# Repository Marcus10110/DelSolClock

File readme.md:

# Del Sol Clock

This is a project to replace the clock in my car with an ESP32 and a small display.

The replacement clock screen will display time, the currently playing music, and iOS notifications.

Bluetooth low energy is used to communicate with a phone.
Note, some services should support any BLE phone, for example the current time service. However the Apple Media Service and the notification service only support iOS.

## Features

### Apple Media Service

This displays the current playback information from the iPhone. It doesn't currently support playback controls (e.g. next/previous track).

[Apple Documentation.](https://developer.apple.com/library/archive/documentation/CoreBluetooth/Reference/AppleMediaService_Reference/Specification/Specification.html#//apple_ref/doc/uid/TP40014716-CH1-SW7)

Special thanks to the following examples. As far as I can tell, this hasn't been implemented using the [Arduino ESP32 board library](https://github.com/espressif/arduino-esp32) before.

- [James Hudson's Apple Notification Center Service](https://github.com/Smartphone-Companions/ESP32-ANCS-Notifications/blob/master/src/ancs_ble_client.cpp) This example finally showed how to solicit services using the Arduino ESP32 library, which is not built-in.
- [John Park's Adafruit Guide to the Apple Media Service Display](https://learn.adafruit.com/now-playing-bluetooth-apple-media-service-display/apple-music-service) This was the first working example I could find. Written in CircutPython.
- [Moddable's Apple Media Service example](https://github.com/Moddable-OpenSource/moddable/blob/6d7f33f8f318663bd5ba8d6ca6536443d42e68ea/modules/network/ble/ams-client/amsclient.js#L129) This was another good example, written in javascript.

### Current Time Service

This gets the current time.

[Current Time Service Documentation](https://www.bluetooth.com/specifications/specs/current-time-service-1-1/)

Note, the documentation is split over several PDFs. See CurrentTimeService.cpp for more documentation links.

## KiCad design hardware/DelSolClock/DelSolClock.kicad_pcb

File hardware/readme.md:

# Hardware

The Del Sol Clock PCBs are designed to be direct replacements for the stock clock PCBs found in the original dash clock.

There are two PCBs in the clock housing. The front PCB, which contains pretty everything, and a rear PCB, which is largely responsible for the electrical connections to the car.

The two PCBs are designed with KiCad. The front PCB is located in the `./DelSolClock` directory, and the rear PCB is located in `./DelSolClock-Rear` directory.

## Front PCB

Schematic:

Divider Circuit:

This divider circuit is used to shift the 12V signal down to 3.3V without engaging over voltage protection. It uses a ~3.6 volt Zener diode to clamp the voltage, which is preferred over regular rail clamps to prevent damage if the supply voltage is not present when a 12V input is applied.

PCB:

## Rear PCB

The rear PCB contains a 12V to 3.3V buck converter module, to provide power to the front PCB, and routes all the car IO signals to the front PCB.

The front PCB is connected to the read PCB with a short 8 pin ribbon cable.

The rear PCB also contains diodes for the Trunk, Roof, and Window signals, to prevent backfeeding into the car's electrical system.

The following signals are provided by the car:

- 12V Power (battery, always hot)
- Ground
- Ignition (IGN)
- Rear Window
- Roof removed
- Trunk Open
- Dash Illumination (ILL)

Rear window, roof removed, and trunk open are open drain signals, which either float or get connected to ground when active. The stock dash clock contained indicator LEDs connected to these signals.

Ignition is also an active high signal, which is only high when the ignition is on. I think it floats when not active.

Dash illumination is connected to the dash's lights, which are dimmable, but only on when the headlights are on. This controlled the brightness of the original dash clock's display. When the headlights are off, the stock clock would run at max brightness.

Schematic:

PCB:

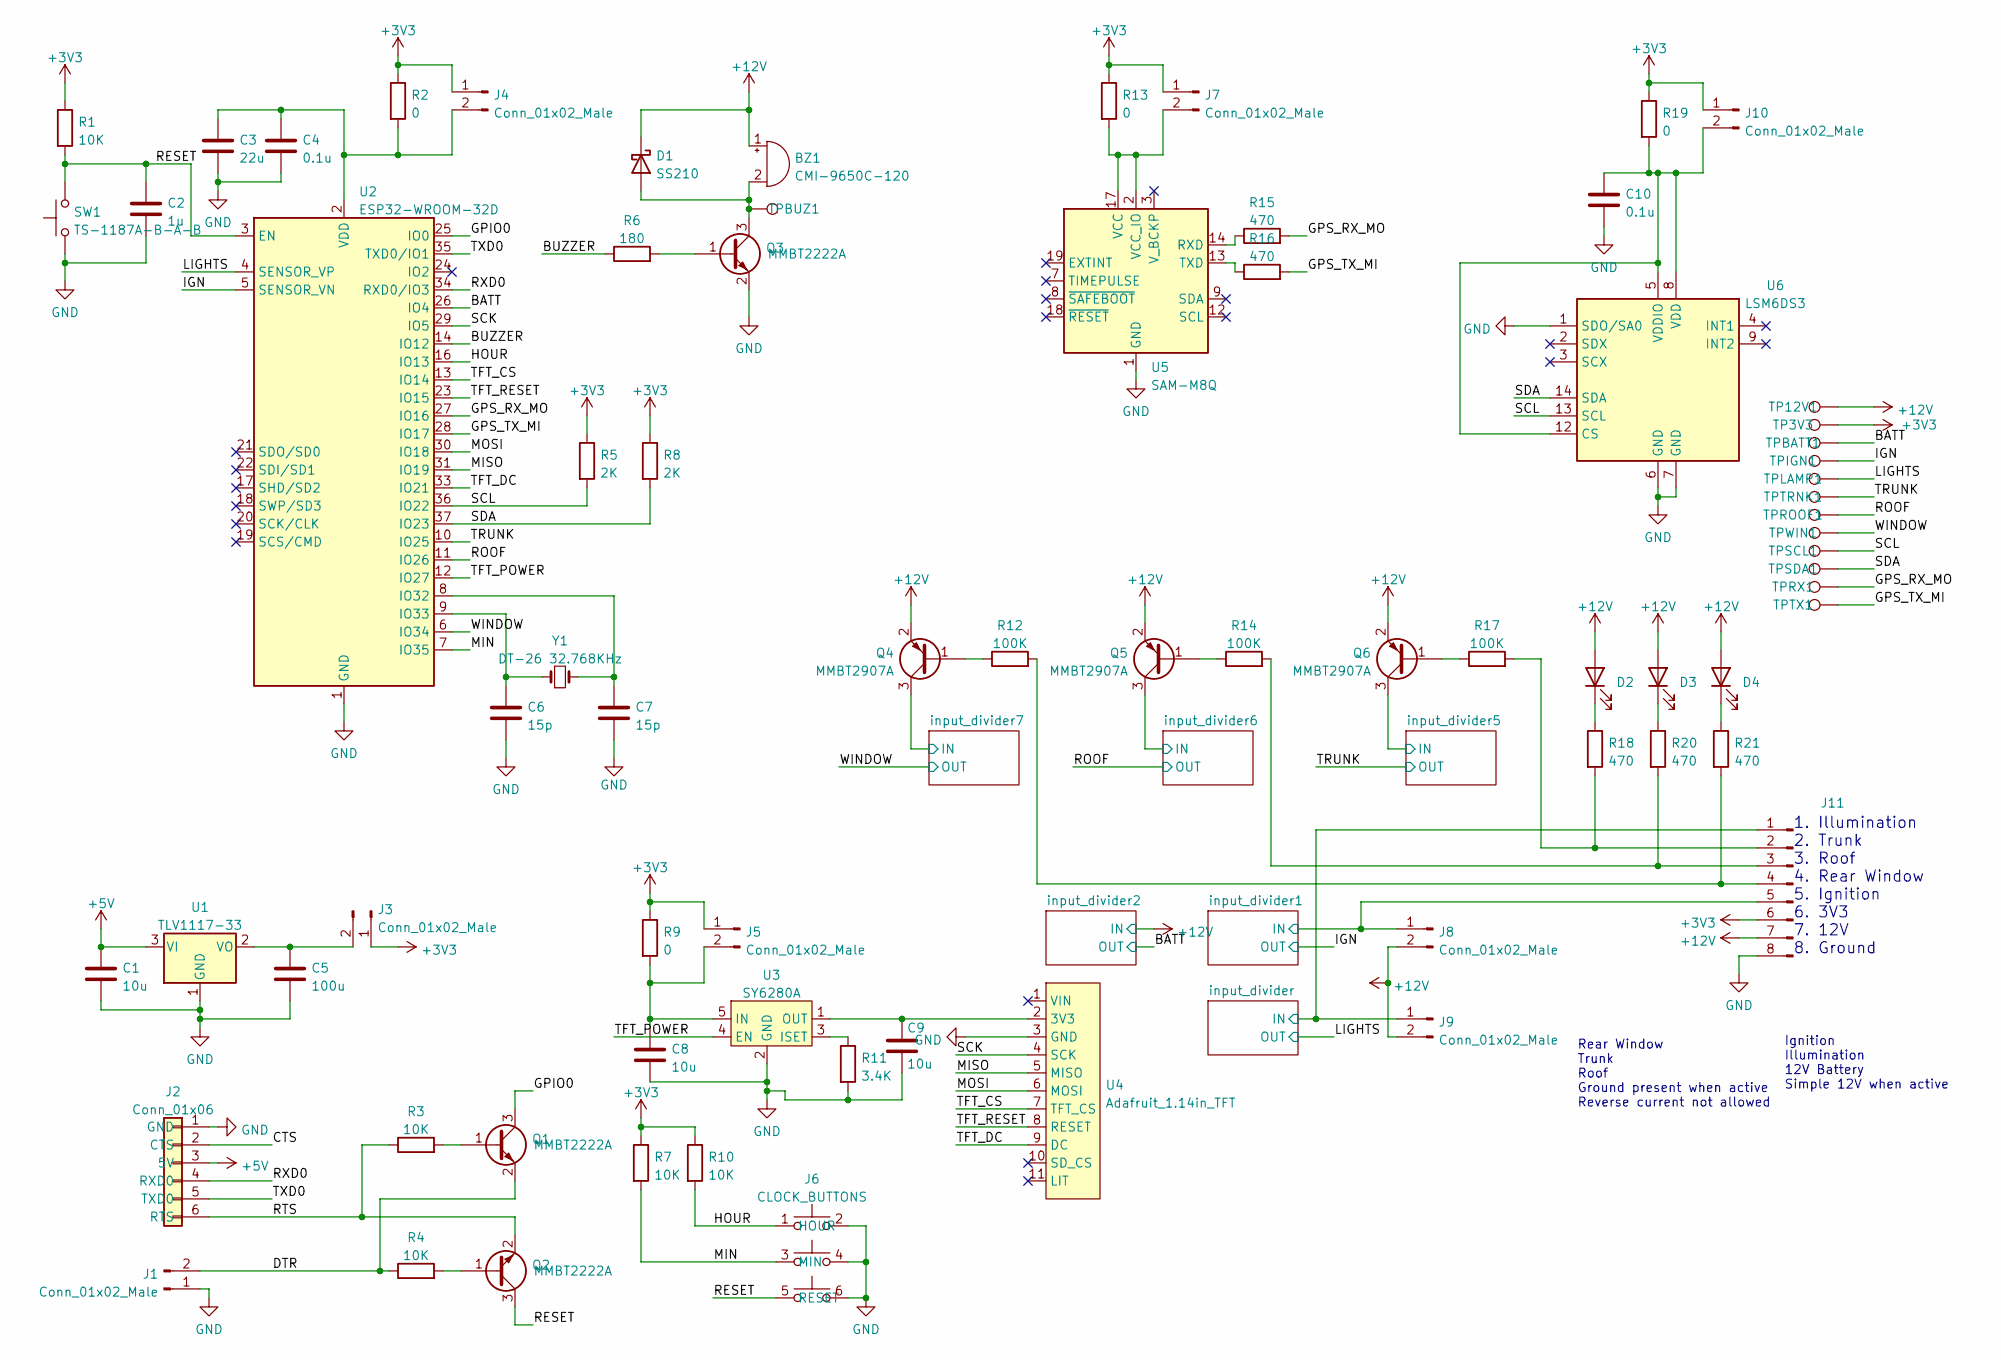
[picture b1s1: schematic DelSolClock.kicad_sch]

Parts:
BZ1: CMI-9650C-120; Buzzer_CUI-CMI-9650C-120
C1, C8, C9: 10u; C_0805_2012Metric_Pad1.18x1.45mm_HandSolder
C2: 1u; C_0805_2012Metric_Pad1.18x1.45mm_HandSolder
C3: 22u; C_0805_2012Metric_Pad1.18x1.45mm_HandSolder
C4, C10: 0.1u; C_0805_2012Metric_Pad1.18x1.45mm_HandSolder
C5: 100u; C_1206_3216Metric_Pad1.33x1.80mm_HandSolder
C6, C7: 15p; C_0805_2012Metric_Pad1.18x1.45mm_HandSolder
D1: SS210; D_SMA_Handsoldering
D2, D3: SSL-LX4673ID-LA20; LED_Rectangular_W3.65mm_L6.15mm
D4: WP132XGD; LED_D3.0mm
J1, J3, J4, J5, J7, J8, J9, J10: Conn_01x02_Male; PinHeader_1x02_P2.54mm_Vertical
J2: Conn_01x06; PinHeader_1x06_P2.54mm_Vertical
J6: CLOCK_BUTTONS; Switch_DelSol
J11: Conn_01x08_Male; PinHeader_1x08_P2.54mm_Vertical
Q1, Q2, Q3: MMBT2222A; SOT-23
Q4, Q5, Q6: MMBT2907A; SOT-23
R1, R3, R4, R7, R10: 10K; R_0805_2012Metric_Pad1.20x1.40mm_HandSolder
R2, R9, R13, R19: 0; R_0805_2012Metric_Pad1.20x1.40mm_HandSolder
R5, R8: 2K; R_0805_2012Metric_Pad1.20x1.40mm_HandSolder
R6: 180; R_0805_2012Metric_Pad1.20x1.40mm_HandSolder
R11: 3.4K; R_0805_2012Metric_Pad1.20x1.40mm_HandSolder
R12, R14, R17: 100K; R_0805_2012Metric_Pad1.20x1.40mm_HandSolder
R15, R16, R18, R20, R21: 470; R_0805_2012Metric_Pad1.20x1.40mm_HandSolder
SW1: TS-1187A-B-A-B; SW_SPST_SKQG_WithoutStem
TP3V3, TP12V1: TestPoint; TestPoint_Keystone_5000-5004_Miniature
TPBATT1: TestPoint; TestPoint_Keystone_5000-5004_Miniature
TPBUZ1: TestPoint; TestPoint_Keystone_5000-5004_Miniature
TPIGN1: TestPoint; TestPoint_Keystone_5000-5004_Miniature
TPLAMP1: TestPoint; TestPoint_Keystone_5000-5004_Miniature
TPROOF1: TestPoint; TestPoint_Keystone_5000-5004_Miniature
TPRX1: TestPoint; TestPoint_Keystone_5000-5004_Miniature
TPSCL1: TestPoint; TestPoint_Keystone_5000-5004_Miniature
TPSDA1: TestPoint; TestPoint_Keystone_5000-5004_Miniature
TPTRNK1: TestPoint; TestPoint_Keystone_5000-5004_Miniature
TPTX1: TestPoint; TestPoint_Keystone_5000-5004_Miniature
TPWIN1: TestPoint; TestPoint_Keystone_5000-5004_Miniature
U1: TLV1117-33; SOT-223
U2: ESP32-WROOM-32D; ESP32-WROOM-32
U3: SY6280A; SOT-23-5
U4: Adafruit_1.14in_TFT
U5: SAM-M8Q; ublox_SAM-M8Q
U6: LSM6DS3; LGA-14_3x2.5mm_P0.5mm_LayoutBorder3x4y
Y1: DT-26 32.768KHz; Crystal_DS26_D2.0mm_L6.0mm_Horizontal_1EP_style1

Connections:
+3V3: J3.1, J4.1, J5.1, J7.1, J10.1, J11.6 (3V3), R1.1, R2.1, R5.1, R7.1, R8.1, R9.1, R10.1, R13.1, R19.1, TP3V3.1
+5V: C1.1, J2.3 (5V), U1.3 (VI)
+12V: BZ1.1 (-), D1.1 (K), D2.2 (A), D3.2 (A), D4.2 (A), J8.2, J9.2, J11.7 (12V), Q4.2 (E), Q5.2 (E), Q6.2 (E), TP12V1.1; also elsewhere on the board
/BATT: TPBATT1.1, U2.26 (IO4); also elsewhere on the board
/BUZZER: R6.1, U2.14 (IO12)
/CTS: J2.2 (CTS)
/DTR: J1.2, Q1.2 (E), R4.1
/GPIO0: Q1.3 (C), U2.25 (IO0)
/GPS_RX_MO: R15.2, TPRX1.1, U2.27 (IO16)
/GPS_TX_MI: R16.2, TPTX1.1, U2.28 (IO17)
/HOUR: J6.1 (HOUR), R10.2, U2.16 (IO13)
/IGN: TPIGN1.1, U2.5 (SENSOR_VN); also elsewhere on the board
/LIGHTS: TPLAMP1.1, U2.4 (SENSOR_VP); also elsewhere on the board
/MIN: J6.3 (MIN), R7.2, U2.7 (IO35)
/MISO: U2.31 (IO19), U4.5 (MISO)
/MOSI: U2.30 (IO18), U4.6 (MOSI)
/RESET: C2.1, J6.5 (RESET), Q2.3 (C), R1.2, SW1.2, U2.3 (EN)
/ROOF: TPROOF1.1, U2.11 (IO26); also elsewhere on the board
/RTS: J2.6 (RTS), Q2.2 (E), R3.1
/RXD0: J2.4 (RXD0), U2.34 (RXD0/IO3)
/SCK: U2.29 (IO5), U4.4 (SCK)
/SCL: R5.2, TPSCL1.1, U2.36 (IO22), U6.13 (SCL)
/SDA: R8.2, TPSDA1.1, U2.37 (IO23), U6.14 (SDA)
/TFT_CS: U2.13 (IO14), U4.7 (TFT_CS)
/TFT_DC: U2.33 (IO21), U4.9 (DC)
/TFT_POWER: U2.12 (IO27), U3.4 (EN)
/TFT_RESET: U2.23 (IO15), U4.8 (RESET)
/TRUNK: TPTRNK1.1, U2.10 (IO25); also elsewhere on the board
/TXD0: J2.5 (TXD0), U2.35 (TXD0/IO1)
/WINDOW: TPWIN1.1, U2.6 (IO34); also elsewhere on the board
/input_divider1/IN: J8.1, J11.5 (Ignition); also elsewhere on the board
/input_divider5/IN: Q6.3 (C); also elsewhere on the board
/input_divider6/IN: Q5.3 (C); also elsewhere on the board
/input_divider7/IN: Q4.3 (C); also elsewhere on the board
/input_divider/IN: J9.1, J11.1 (Illumination); also elsewhere on the board
GND: C1.2, C2.2, C3.2, C4.2, C5.2, C6.2, C7.2, C8.2, C9.2, C10.2, J1.1, J2.1 (GND), J6.2, J6.4, J6.6, J11.8 (GND), Q3.2 (E), R11.2, SW1.1, U1.1 (GND), U2.1 (GND), U2.15 (GND), U2.38 (GND), U2.39 (GND), U3.2 (GND), U4.3 (GND), U5.1 (GND), U5.4 (GND), U5.5 (GND), U5.6 (GND), U5.10 (GND), U5.11 (GND), U5.15 (GND), U5.16 (GND), U5.20 (GND), U6.1 (SDO/SA0), U6.6 (GND), U6.7 (GND); also elsewhere on the board
unnamed: BZ1.2 (+), D1.2 (A), Q3.3 (C), TPBUZ1.1
unnamed: D2.1 (K), R18.1
unnamed: D3.1 (K), R20.1
unnamed: D4.1 (K), R21.1
unnamed: C5.1, J3.2, U1.2 (VO)
unnamed: C3.1, C4.1, J4.2, R2.2, U2.2 (VDD)
unnamed: C8.1, J5.2, R9.2, U3.5 (IN)
unnamed: J7.2, R13.2, U5.2 (VCC_IO), U5.17 (VCC)
unnamed: C10.1, J10.2, R19.2, U6.5 (VDDIO), U6.8 (VDD), U6.12 (CS)
unnamed: J11.4 (Rear_Window), R12.2, R21.2
unnamed: J11.3 (Roof), R14.2, R20.2
unnamed: J11.2 (Trunk), R17.2, R18.2
unnamed: Q1.1 (B), R3.2
unnamed: Q2.1 (B), R4.2
unnamed: Q3.1 (B), R6.2
unnamed: Q4.1 (B), R12.1
unnamed: Q5.1 (B), R14.1
unnamed: Q6.1 (B), R17.1
unnamed: C7.1, U2.8 (IO32), Y1.2
unnamed: C6.1, U2.9 (IO33), Y1.1
unnamed: R11.1, U3.3 (ISET)
unnamed: C9.1, U3.1 (OUT), U4.2 (3V3)
unnamed: R15.1, U5.14 (RXD)
unnamed: R16.1, U5.13 (TXD)

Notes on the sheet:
Rear Window Trunk Roof Ground present when active Reverse current not allowed
1. Illumination 2. Trunk 3. Roof 4. Rear Window 5. Ignition 6. 3V3 7. 12V 8. Ground
Ignition Illumination 12V Battery Simple 12V when active

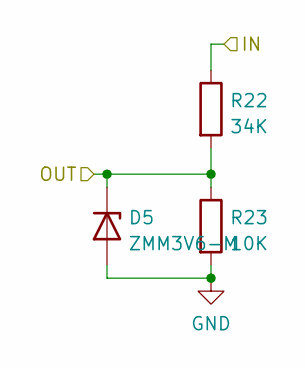
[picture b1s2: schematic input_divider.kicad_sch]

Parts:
D5: ZMM3V6-M; D_MiniMELF
R22: 34K; R_0805_2012Metric_Pad1.20x1.40mm_HandSolder
R23: 10K; R_0805_2012Metric_Pad1.20x1.40mm_HandSolder

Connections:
/LIGHTS: D5.1 (K), R22.2, R23.1; also elsewhere on the board
/input_divider/IN: R22.1; also elsewhere on the board
GND: D5.2 (A), R23.2; also elsewhere on the board

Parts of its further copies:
D6, D7, D8, D9, D10: ZMM3V6-M; D_MiniMELF
R24, R26, R28, R30, R32: 34K; R_0805_2012Metric_Pad1.20x1.40mm_HandSolder
R25, R27, R29, R31, R33: 10K; R_0805_2012Metric_Pad1.20x1.40mm_HandSolder

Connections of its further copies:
+12V: R26.1; also elsewhere on the board
/BATT: D7.1 (K), R26.2, R27.1; also elsewhere on the board
/IGN: D6.1 (K), R24.2, R25.1; also elsewhere on the board
/ROOF: D8.1 (K), R28.2, R29.1; also elsewhere on the board
/TRUNK: D10.1 (K), R32.2, R33.1; also elsewhere on the board
/WINDOW: D9.1 (K), R30.2, R31.1; also elsewhere on the board
/input_divider1/IN: R24.1; also elsewhere on the board
/input_divider5/IN: R32.1; also elsewhere on the board
/input_divider6/IN: R28.1; also elsewhere on the board
/input_divider7/IN: R30.1; also elsewhere on the board
GND: D6.2 (A), D7.2 (A), D8.2 (A), D9.2 (A), D10.2 (A), R25.2, R27.2, R29.2, R31.2, R33.2; also elsewhere on the board

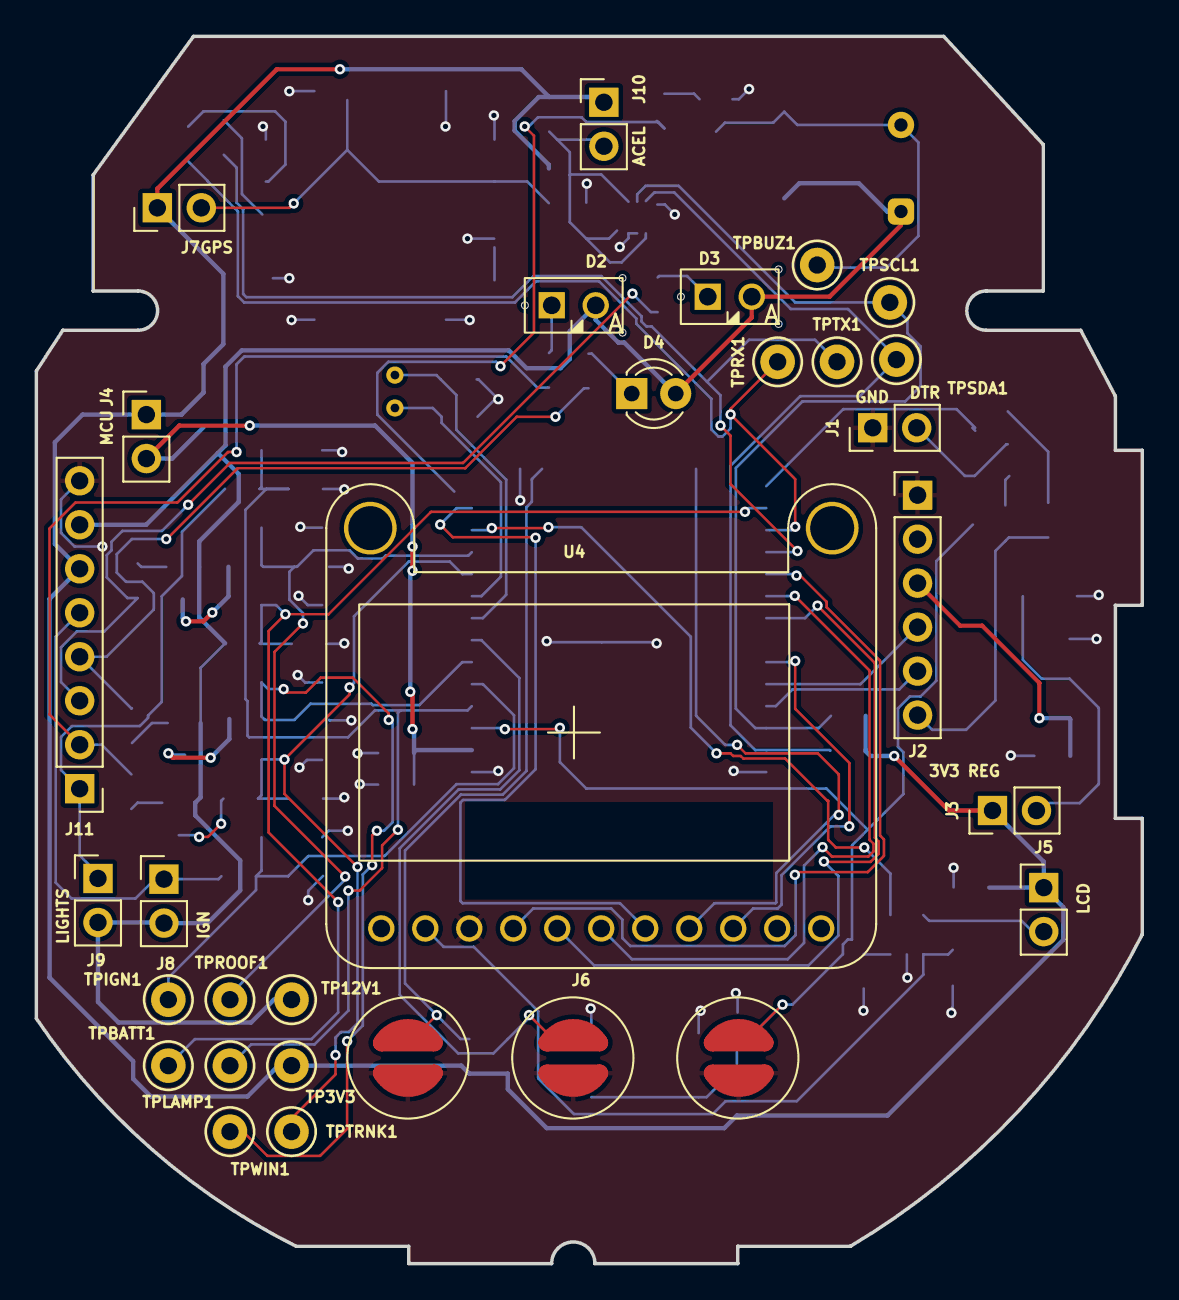
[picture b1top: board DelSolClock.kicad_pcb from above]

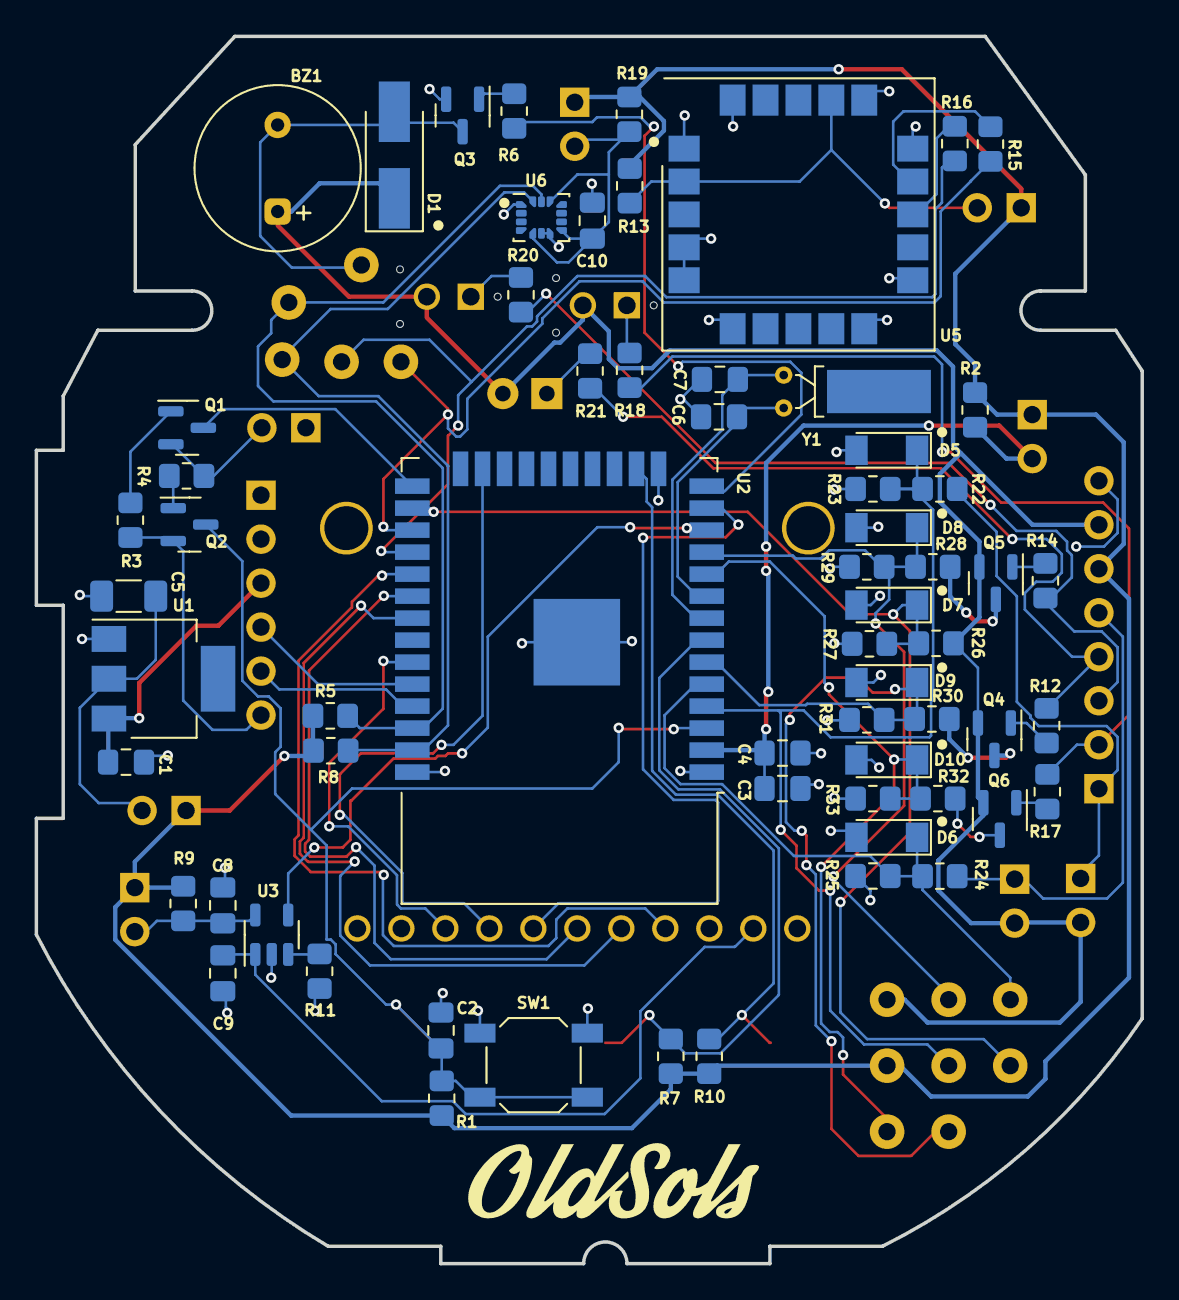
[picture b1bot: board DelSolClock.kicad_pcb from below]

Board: 2 copper layers, 63.8 x 70.9 mm, 92 parts (64 on the bottom side), 59 nets.

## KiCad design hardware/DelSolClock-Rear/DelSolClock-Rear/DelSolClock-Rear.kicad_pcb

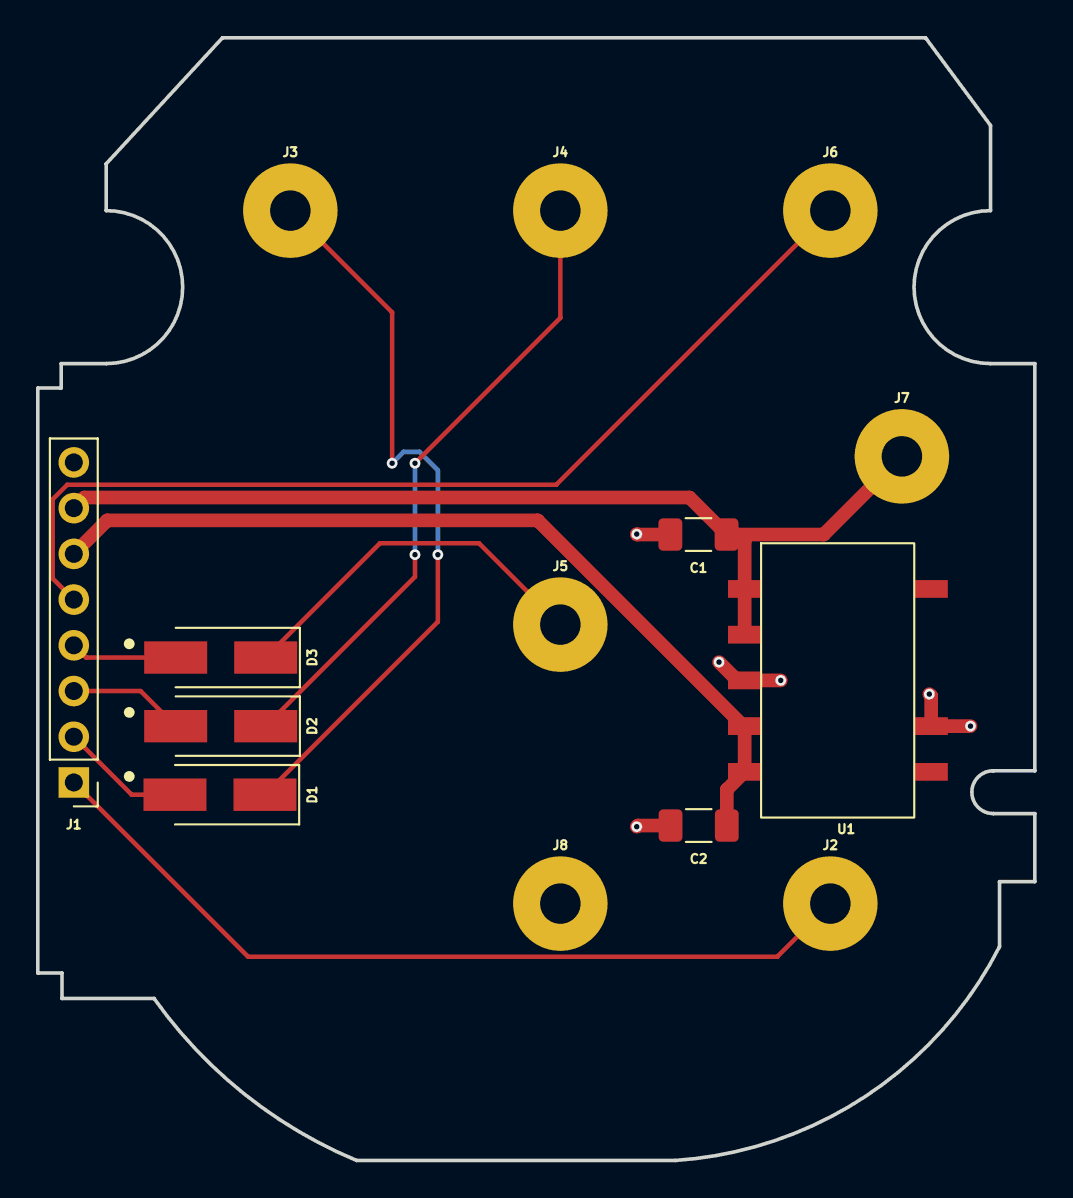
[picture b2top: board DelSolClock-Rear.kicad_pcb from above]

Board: 2 copper layers, 55.4 x 62.4 mm, 14 parts (0 on the bottom side), 11 nets.

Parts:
C1: 10u; C_1206_3216Metric_Pad1.33x1.80mm_HandSolder
C2: 22u; C_1206_3216Metric_Pad1.33x1.80mm_HandSolder
D1, D2, D3: D_Schottky; D_SMA_Handsoldering
J1: Conn_01x08; PinHeader_1x08_P2.54mm_Vertical
J2, J3, J4, J5, J6, J7, J8: Terminal_Spring_Del_Sol
U1: K7803T-500R3

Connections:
+3V3: C2.1, J1.6, U1.4 (+Vout), U1.5 (+Vout)
+12V: C1.1, J1.7, J7.1, U1.1 (+Vin), U1.2 (+Vin)
/IGN: J1.5, J6.1
/ILL: J1.1, J2.1
/ROOF: D2.1 (K), J4.1
/TRUNK: D1.1 (K), J3.1
/WINDOW: D3.1 (K), J5.1
GND: C1.2, C2.2, J1.8, J8.1, U1.3 (GND), U1.7 (GND)
unnamed: D1.2 (A), J1.2
unnamed: D2.2 (A), J1.3
unnamed: D3.2 (A), J1.4

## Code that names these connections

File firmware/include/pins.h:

#pragma once
#include <cstdint>


#define REV2
namespace Pin
{
    // TFT & SD Card
    constexpr int8_t TftReset = 15;
    constexpr int8_t TftCs = 14;
    constexpr int8_t TftDc = 21;
    constexpr int8_t TftPower = 27;
    // SPI
    constexpr int8_t Sck = 5;
    constexpr int8_t Miso = 19;
    constexpr int8_t Mosi = 18;
    // Car Pins
    constexpr int8_t Battery = 4;
    constexpr int8_t Illumination = 36;
    constexpr int8_t Ignition = 39;
    constexpr int8_t RearWindow = 34;
    constexpr int8_t Trunk = 25;
    constexpr int8_t Roof = 26;
    // Clock Pins
    constexpr int8_t Hour = 13;
    constexpr int8_t Minute = 35; //  the Feather connects pin 35 to VBAT divider.
    // Other
    constexpr int8_t Buzzer = 12; // internal boot-related pull down. Use as output only.
    // GPS
#ifdef REV2
    constexpr int8_t GpsRx = 16;
    constexpr int8_t GpsTx = 17;
#else
    // (note, these are the default I2C pins)
    constexpr int8_t GpsRx = 22;
    constexpr int8_t GpsTx = 23;
#endif
}

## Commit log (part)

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2021-08-28 First commit. very crude BLE proof of concept is working.
2021-08-28 big refactor. Moved the Apple Media Service and the Current Time Service into new files, and cleaned up their usage. added a readme.
2021-08-28 added a I2C OLED display. I'm about to replace it with a TFT.
2021-08-29 switched to a TFT display. Not the final display, but it's what I'll use till the real ones arrive.
2021-10-05 added hardware documents. This include the first (only) revision of the rear PCB, and the second (latest) revision of the front PCB.
2021-10-05 lots of progress on the code, but far from the latest. Also added the assets that need to be downloaded to the ESP32.
2021-10-05 added CAD screenshot and link.
2021-10-08 Big refactor! Lots left to do.
2021-10-08 added basic GPS support, works great!
2021-10-08 fixed last line of the TFT display. Fixed keeping the backlight off while sleeping.
2021-10-09 GPS cleaned up and GPS sleep/wake working. Still has the testing sleep code, need to replace that with propper application code next.
2021-10-09 power management is working as required. Added new splash screen added buzzer alarm.
2021-10-10 firmware is pretty much good to go. Lights alarm working well, BLE reporting vehicle status. I still need to fix the BLE connection failure problem we see from time to time.
2021-10-10 xamarin app first commit. Still has a bunch of junk, and only has 1 feature, but it's working! ish.
2021-10-10 fixed compiler error (Linux/mac) added CI scripts added git ignore
2021-10-10 switched on first CI attempt.
2021-10-10 add release creation
2021-10-10 attempting to get tags to build.
2021-10-10 updated release tag filter. removed normal artifact creation.
2021-10-10 general cleanup. added logger page. removed example pages from the tabs, but haven't deleted them yet.
2021-10-16 added release browser to phone app. Only tested in simulator so far. Haven't added upload support yet.
2021-10-18 added BLE OTA updates to the backend. TODO: add CI integration for version.h
2021-10-18 added basic OTA support to the mobile app.
2021-10-26 CI should now generate version.h
2022-01-16 updated display to always buffer using a canvas. This removes flickering!
2022-01-16 improve display of speed and music.
2022-01-16 improved buzzer, and fixed GPS flicker
2022-03-30 started new revision, this time in kicad 6! Schematic is done, parts are placed on PCB, but routing has not started yet. I do have jlcpcb setup for fabrication.
2022-03-30 added jlcpcb database
2022-04-01 more progress on layout. Not done yet.
2022-04-06 most of routing complete, still more work to do.
2022-04-06 added logo, finished layout, ordered board.
2022-04-09 added rear PCB. Big problem: the power supply is too tall to fit in between the boards. we'll need to figure something out.
    Also, we should make it easier to power when debugging somehow. Switch and connector?
2022-06-26 HW updates after testing the last prototype round. fixed PNP and NPN transistor pin mapping error (whoops) added keepouts and moved components inside of the board area. added holes for the rectangle 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
    Main remaining item is to adjust LED placement after testing.
2023-04-19 just shipped the latest revision (Rev 4?)
2023-05-01 updated arduino code to latest, which includes new pinout for rev 4. Still lots left to do.
2023-06-12 added new screens and simulation mode. confirmed that original display system still works on hardware.
2023-06-21 switched over to display2. Note, main.cpp was not committed, because it broke a lot of stuff to demo the display on hardware.
2024-04-07 Lots of misc in-progress stuff, most of which was abandoned. I need to get this committed so I can start cleaning up.
    Added wokwi, added a demo mode for easier screen testing, pulled in all sorts of stuff, left it half way though a big migration of some sort.
2024-04-07 removed wokwi / simulation support. moved an old font file around
2024-04-08 removed original altium project.
2024-04-08 moved kicad version into hardware folder.
2024-04-08 ported firmware over to platform IO. went pretty smoothly! Did some minor cleanup (mainly filename changes)
2024-04-08 removed old source.
2024-04-08 update CI to build platform IO (hopefully) Note it no longer deploys.
2024-04-08 moved demo to a new file. also tested demo mode on the HW, works well!
2024-04-08 change directory for firmware build.
2024-04-08 re-enabled support for publishing tags.
2024-04-08 added quarter mile timer. added ability to click through screens with hour button.
2024-04-08 added g-force to the status screen.
2024-04-10 it's working pretty well! added support for selectively deleting images from RAM after drawing them, instead of caching them. This lets us draw the splash screen then delete it, so there is still RAM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
2024-04-10 removed font test dead code.
2024-04-10 added a simple logger library, and converted all serial.print calls to use it.
2024-04-10 misc small changes. mainly just found and replaced a few old log calls.
2025-01-14 updated to KiCad 8
2025-01-14 added missing 3V3 connection to the accelerometer CS pin, to select I2C mode.
2025-05-31 add instructions and scripts, etc, to make it easy to build esp32 / arduino / platformIO support with the external 32 KHz crystal.
2025-06-02 switched to custom build of esp32-arduino & bootloader, to support external 32k crystal. did not commit the actual libs zip because it's > 300 MB, above github file size limit
2025-06-02 switched to custom build of esp32-arduino & bootloader, to support external 32k crystal.
2025-06-02 added apple notifications, and displays for notifications and for driving directions. It still has some bugs, but it's working!
2025-06-05 .net maui app first commit. minimal progress.
2025-08-27 checkpoint: about to have claude take over.
2025-08-27 basic device connectivity is working!
2025-08-29 update images for FW
2025-08-29 notifications now keep priority notifications for an extra 5 seconds. also, directions notifications filtering was improved.
2025-08-29 bluetooth advertisement cleanup
2025-08-29 added new screen for the GMeter, solved the image problem, added a pre-load, etc.
2025-08-29 added new motion vector transform, and more.
2025-08-29 GPS code update
2025-08-29 move framework to s3
2025-08-29 fix case
2025-08-29 update page UI refresh.
2025-08-30 OTA FW update now reasonably fast, with good logging. The "complete" notification now makes it back to the app too. Added but commented out channel parameter changes, did not make much impact.
2025-08-30 FW update basically working from the app.
2025-08-30 removed old placeholder DelSolConnection class.
2025-08-30 connection cycle and other misc improvements.
2025-08-30 added scan filter, reduced timeout.
2025-08-31 the app launches on my iphone!
2025-08-31 fixed iOS permissions thingy
2025-08-31 added a watchdog, and turned off DISABLE_SLEEP
2025-08-31 Fix some of our WDT timeouts. re-calibrated the battery voltage, this time 1V to 14V. added basic debug status service, lots left to do. added missing battery voltage characteristic, that's working. 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
2025-09-01 beginnings of crash downloading.
2025-09-01 added crash downloading and misc debug commands to app.
2025-09-01 all debug commands working!
2025-09-01 removed the disable sleep command again.
2025-09-01 minor cleanup
2025-09-01 fix version write
2025-09-02 the firmware seems to work OK!
2025-09-02 support BLE retry in the app, fixes iOS problem when BLE isn't available at launch.
2025-09-02 fix default screen
2025-09-02 publish both bin and elf
2025-09-08 keep 10 notifications, show notification count
2026-02-18 added hardware readme.
2026-06-16 updated link
2026-06-19 add reconnect button.
2026-06-19 remove the old C# apps, in favor of the webapp.
2026-06-19 added font conversion tool
2026-06-20 finished display / screen migration inside the firmware.
2026-06-20 added core of the UiDesigner.
2026-06-20 added readme to the UI designer
2026-06-20 regen images on save
2026-06-20 webapp boilerplate
2026-06-20 navigation fetch and simplification
2026-06-20 add route matcher C++ and ts tests.
2026-06-20 added navigation service to the firmware, and it works!
2026-06-20 added missing file
2026-06-20 add basic route support to typescript.
2026-06-20 turn off apple notification system
2026-06-20 add new navigation UI (text only)
2026-06-20 move helpers into helpers file.
2026-06-21 add navigation to web application.
2026-06-21 very basic road rendering working! lots left to do.
2026-06-21 added nav bars.
2026-06-21 turned on new turn by turn nav in fw. not tested yet.
2026-06-21 add debug features to the web app for ble
2026-06-21 more BLE debugging
2026-06-21 fix the BLE issue
2026-06-21 touch up the forget button
2026-06-21 added gps debug improvements.
2026-06-21 big navigation glow-up
2026-06-21 added car sprite. looking great!
2026-06-21 improved video speed.
2026-06-21 added spiffs hash function.
2026-06-21 add proto v2 for loading firmware and spiffs
2026-06-21 added debugging to the FW update button
2026-06-21 fix FW download.
2026-06-21 added web service to proxy downloads. added logging to FW downloader. added warmup system to help deal with free-tier service.
2026-06-21 added github PAT to try and make downloads work.
2026-06-21 show hash, include speed and time remaining.
2026-06-21 trying to fix FW upload
2026-06-21 re-enabled sleep
2026-06-22 added tabs to the webapp
2026-06-22 added day theme and auto theme changing
2026-06-29 add bezel editor to web page, and to draw system
2026-06-29 update all screens to respect bezel better. also update the ui designer to support bezel and include missing screens
2026-06-29 added a GPS recorder. not yet tested.
2026-06-29 add debugging client side
